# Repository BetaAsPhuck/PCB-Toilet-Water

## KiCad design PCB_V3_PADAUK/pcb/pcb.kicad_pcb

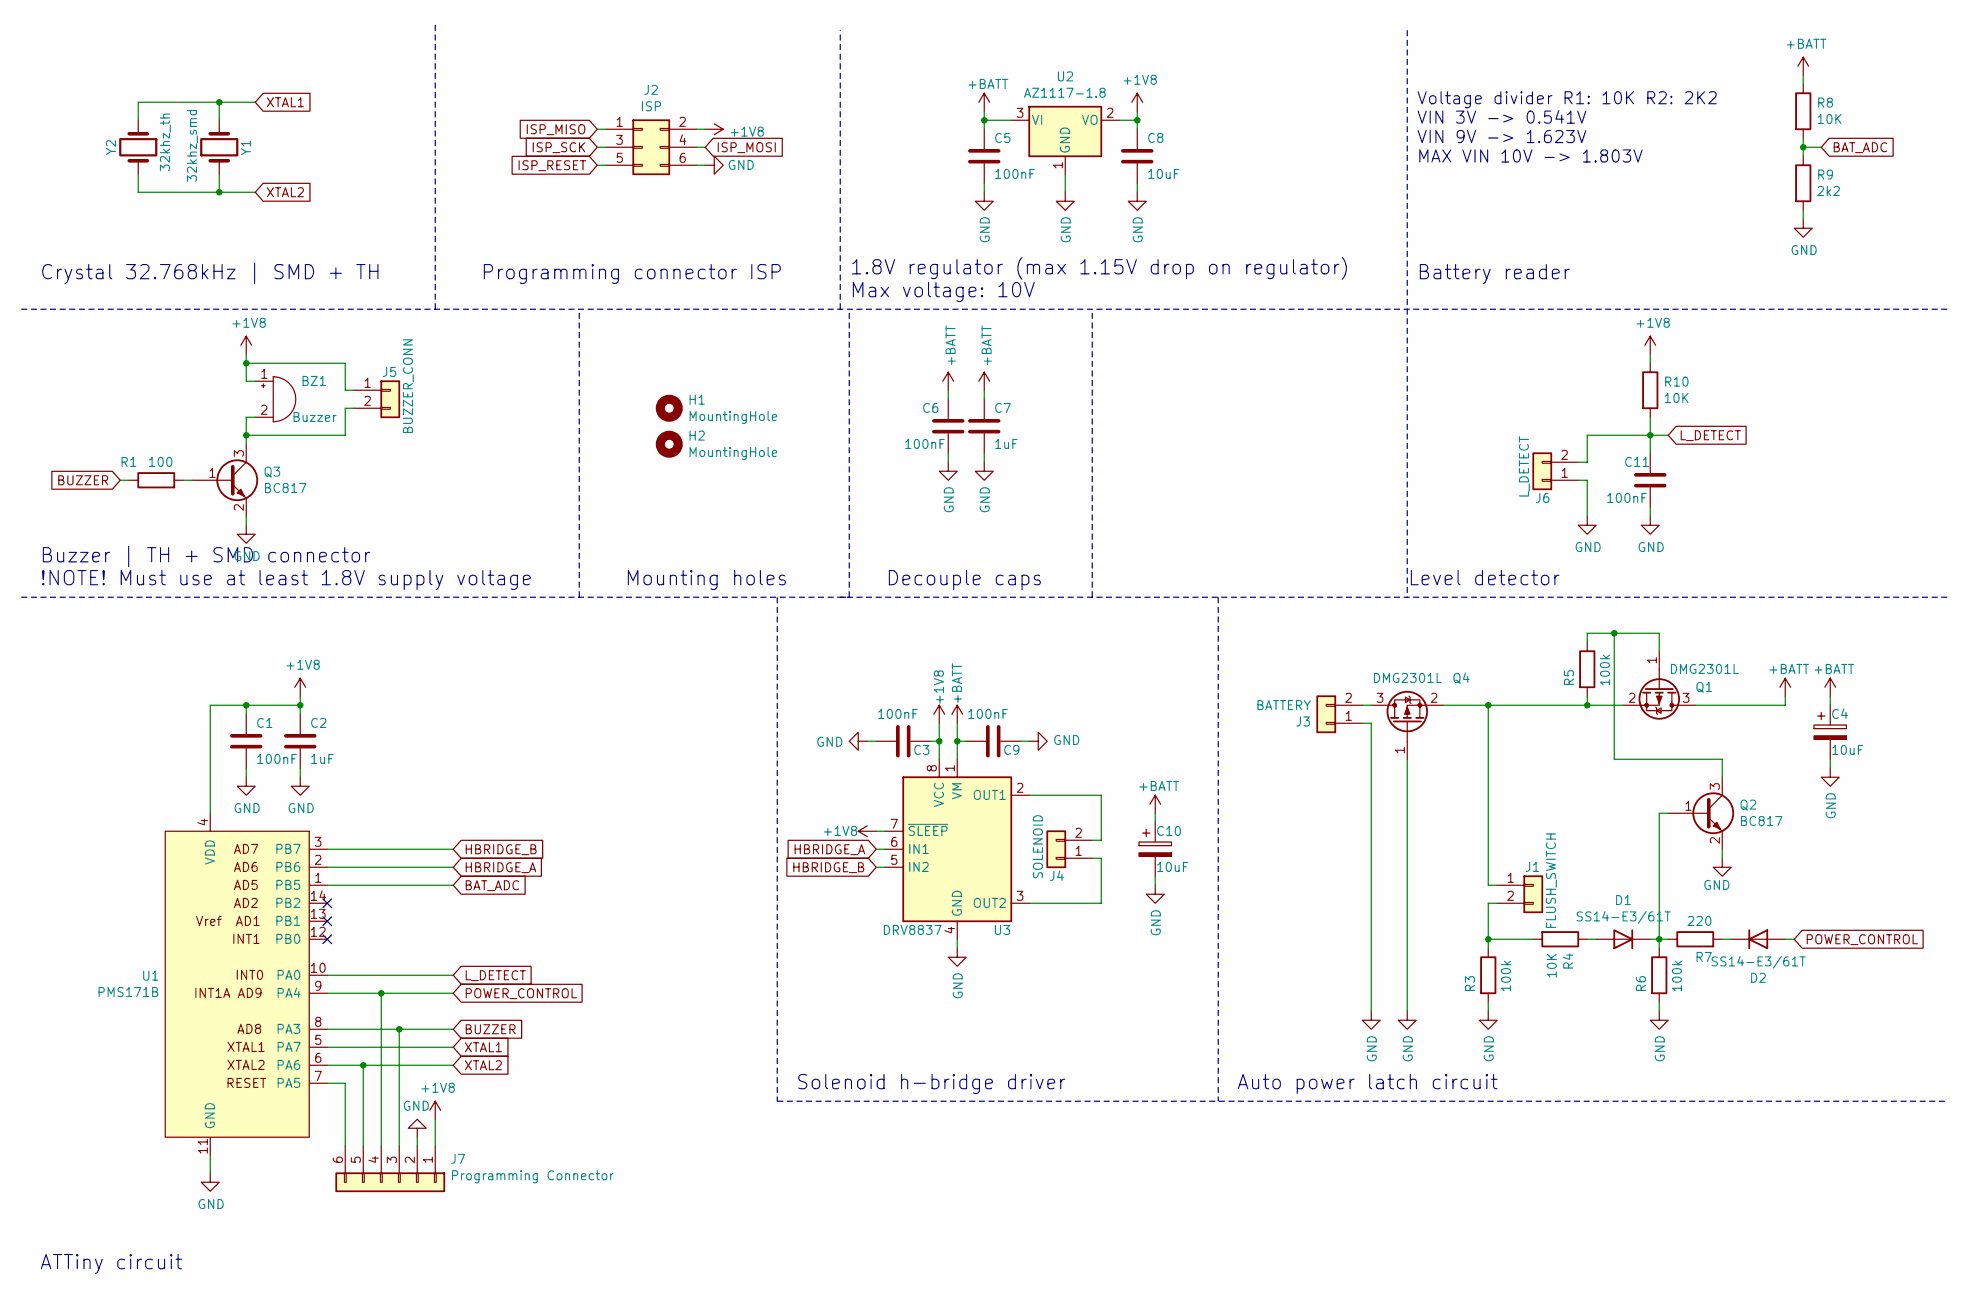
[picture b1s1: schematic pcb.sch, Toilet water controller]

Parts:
BZ1: Buzzer; MagneticBuzzer_PUI_AT-0927-TT-6-R; PartNo MCABT-411-RC
C1, C3, C5, C6, C9, C11: 100nF; C_0603_1608Metric; PartNo C0603C104K3RAC7411
C2, C7: 1uF; C_0603_1608Metric; PartNo CC0603KRX5R6BB105
C4, C10: 10uF; CP_EIA-3216-10_Kemet-I; PartNo 293D106X9016A2TE3
C8: 10uF; C_0603_1608Metric; PartNo CC0603MRX5R5BB106
D1, D2: SS14-E3/61T; D_SMA; PartNo DFLS1100-7
H1, H2: MountingHole; MountingHole_3.5mm
J1: FLUSH_SWITCH; conn_solder
J2: ISP; PinHeader_2x03_P2.54mm_Vertical
J3: BATTERY; 9v battery con
J4: SOLENOID; conn_solder
J5: BUZZER_CONN; conn_solder
J6: L_DETECT; conn_solder
J7: Programming Connector; PinHeader_2x03_P2.54mm_Vertical
Q1, Q4: DMG2301L; SOT-23; PartNo DMG2301L-7
Q2, Q3: BC817; SOT-23; PartNo BC817,215
R1: 100; R_0603_1608Metric; PartNo RC0603FR-07100RL
R3, R5, R6: 100k; R_0603_1608Metric; PartNo RC0603FR-07100KL
R4, R8, R10: 10K; R_0603_1608Metric; PartNo CRCW060310K0FKEA
R7: 220; R_0603_1608Metric; PartNo MCWR06X2200FTL
R9: 2k2; R_0603_1608Metric; PartNo RC0603JR-072K2L
U1: PMS171B; SOIC-14_3.9x8.7mm_P1.27mm
U2: AZ1117-1.8; SOT-223; PartNo SPX1117M3-L-1-8/TR
U3: DRV8837; WSON-8-1EP_2x2mm_P0.5mm_EP0.9x1.6mm; PartNo DRV8837DSGR
Y1: 32khz_smd; Crystal_SMD_SeikoEpson_MC306-4Pin_8.0x3.2mm; PartNo X32K768L104
Y2: 32khz_th; Crystal_DS26_D2.0mm_L6.0mm_Horizontal_1EP_style1

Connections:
+1V8: BZ1.1 (-), C1.1, C2.1, C3.1, C8.1, J2.2, J5.1, J7.1, R10.1, U1.4 (VDD), U2.2 (VO), U3.7 (~SLEEP), U3.8 (VCC); also elsewhere on the board
+BATT: C4.1, C5.1, C6.1, C7.1, C9.2, C10.1, Q1.3 (D), R8.1, U2.3 (VI), U3.1 (VM)
BAT_ADC: R8.2, R9.1, U1.1 (PB5)
BUZZER: J7.3, R1.1, U1.8 (PA3)
HBRIDGE_A: U1.2 (PB6), U3.6 (IN1)
HBRIDGE_B: U1.3 (PB7), U3.5 (IN2)
L_DETECT: C11.1, J6.2, R10.2, U1.10 (PA0)
unnamed: BZ1.2 (+), J5.2, Q3.3 (C)
unnamed: D1.1 (K), Q2.1 (B), R6.1, R7.1
unnamed: D1.2 (A), R4.1
unnamed: D2.1 (K), R7.2
unnamed: J1.1, Q1.2 (S), Q4.2 (S), R5.2
unnamed: J1.2, R3.1, R4.2
unnamed: J3.2, Q4.3 (D)
unnamed: J4.1, U3.3 (OUT2)
unnamed: J4.2, U3.2 (OUT1)
unnamed: Q1.1 (G), Q2.3 (C), R5.1
unnamed: Q3.1 (B), R1.2
POWER_CONTROL: D2.2 (A), J7.4, U1.9 (PA4)
XTAL1: U1.5 (PA7), Y1.2, Y2.1
XTAL2: J7.5, U1.6 (PA6), Y1.1, Y2.2

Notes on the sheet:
Programming connector ISP
Buzzer | TH + SMD connector !NOTE! Must use at least 1.8V supply voltage
1.8V regulator (max 1.15V drop on regulator) Max voltage: 10V
Solenoid h-bridge driver
Battery reader
ATTiny circuit
Mounting holes
Decouple caps
Crystal 32.768kHz | SMD + TH
Voltage divider R1: 10K R2: 2K2 VIN 3V -> 0.541V VIN 9V -> 1.623V MAX VIN 10V -> 1.803V
Level detector
Auto power latch circuit

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
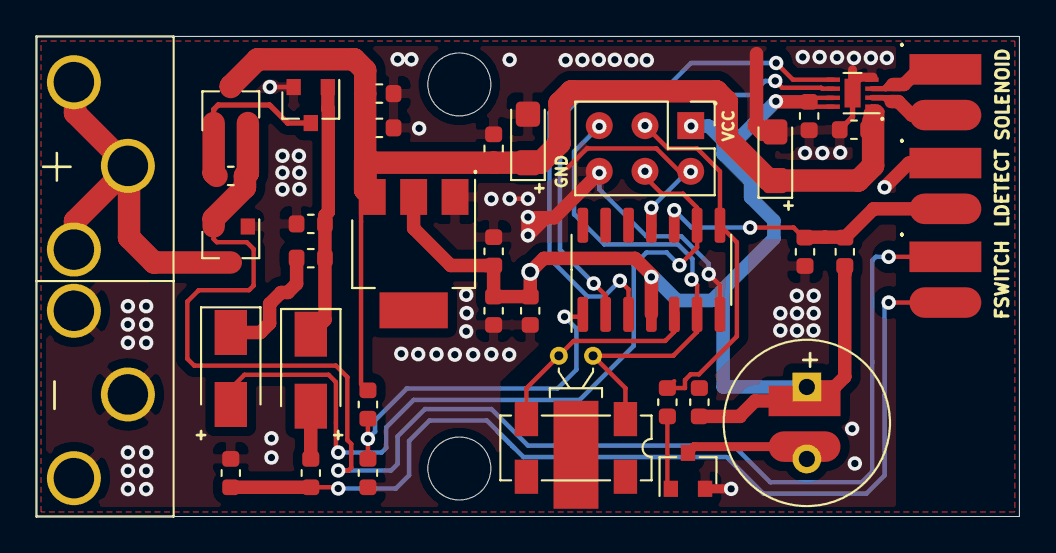
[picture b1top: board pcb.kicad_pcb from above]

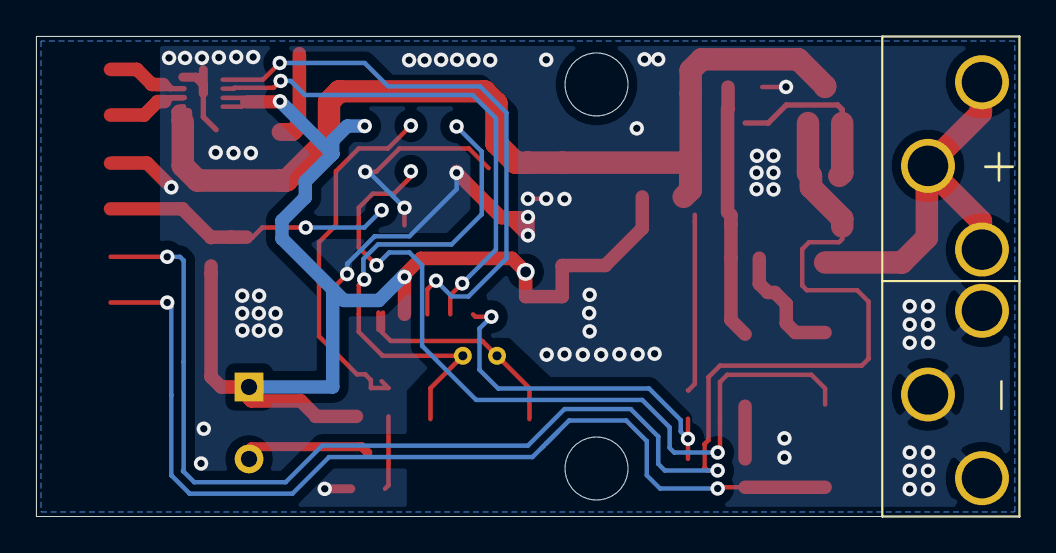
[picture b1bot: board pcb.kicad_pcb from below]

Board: 2 copper layers, 54.6 x 26.7 mm, 41 parts (2 on the bottom side), 22 nets.

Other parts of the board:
R2: 10K; R_0603_1608Metric

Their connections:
+1V8: R2.2; also elsewhere on the board

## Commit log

2020-07-10 Create Programming unit
2020-07-10 Add files via upload
    Via updated
2020-07-10 Programming unit
    Gerber files
